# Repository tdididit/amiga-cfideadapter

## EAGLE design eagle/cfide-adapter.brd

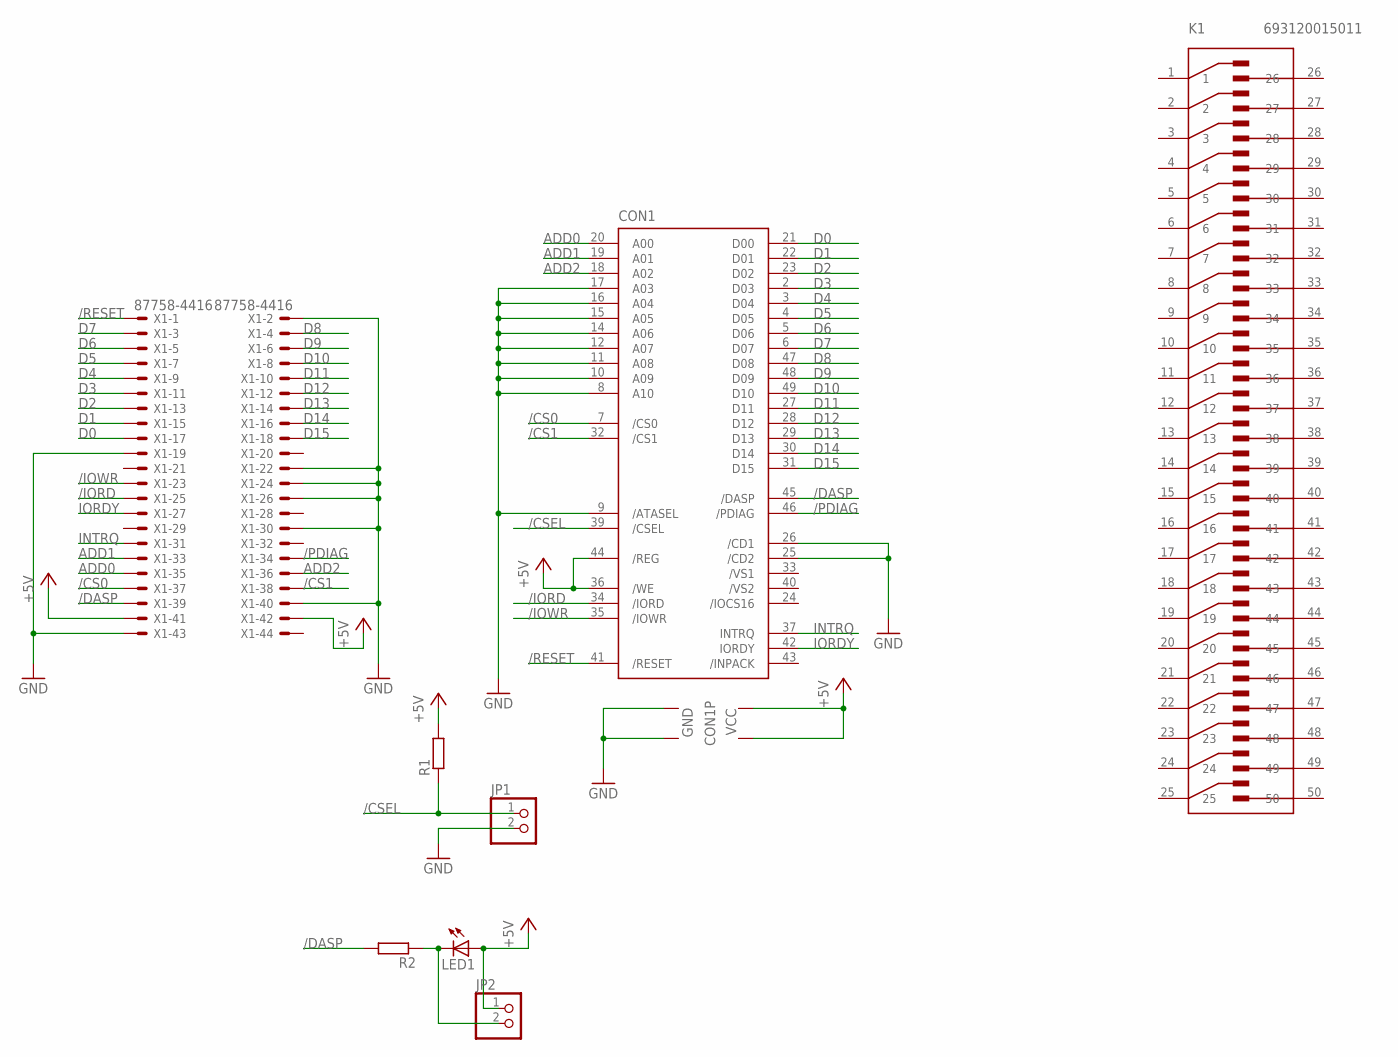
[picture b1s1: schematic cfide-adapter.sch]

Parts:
CON1: CF-CARD-IDE_MODE; MI20-50PD-SF
JP1, JP2: HEADER-1X2ROUND; 1X02_ROUND
K1: 693120015011
LED1: LEDCHIP-LED0603; CHIP-LED0603
R1, R2: R-EU_R0603; R0603
X1: 87758-4416

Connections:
+5V: CON1.13 (VCC2), CON1.36 (/WE), CON1.38 (VCC1), CON1.44 (/REG), JP2.1, LED1.A, R1.2, X1.41, X1.42
/CS0: CON1.7 (/CS0), X1.37
/CS1: CON1.32 (/CS1), X1.38
/CSEL: CON1.39 (/CSEL), JP1.1, R1.1
/DASP: CON1.45 (/DASP), R2.2, X1.39
/IORD: CON1.34 (/IORD), X1.25
/IOWR: CON1.35 (/IOWR), X1.23
/PDIAG: CON1.46 (/PDIAG), X1.34
/RESET: CON1.41 (/RESET), X1.1
ADD0: CON1.20 (A00), X1.35
ADD1: CON1.19 (A01), X1.33
ADD2: CON1.18 (A02), X1.36
D0: CON1.21 (D00), X1.17
D1: CON1.22 (D01), X1.15
D2: CON1.23 (D02), X1.13
D3: CON1.2 (D03), X1.11
D4: CON1.3 (D04), X1.9
D5: CON1.4 (D05), X1.7
D6: CON1.5 (D06), X1.5
D7: CON1.6 (D07), X1.3
D8: CON1.47 (D08), X1.4
D9: CON1.48 (D09), X1.6
D10: CON1.49 (D10), X1.8
D11: CON1.27 (D11), X1.10
D12: CON1.28 (D12), X1.12
D13: CON1.29 (D13), X1.14
D14: CON1.30 (D14), X1.16
D15: CON1.31 (D15), X1.18
GND: CON1.1 (GND1), CON1.8 (A10), CON1.9 (/ATASEL), CON1.10 (A09), CON1.11 (A08), CON1.12 (A07), CON1.14 (A06), CON1.15 (A05), CON1.16 (A04), CON1.17 (A03), CON1.25 (/CD2), CON1.26 (/CD1), CON1.50 (GND2), JP1.2, X1.2, X1.19, X1.22, X1.24, X1.26, X1.30, X1.40, X1.43
INTRQ: CON1.37 (INTRQ), X1.31
IORDY: CON1.42 (IORDY), X1.27
unnamed: JP2.2, LED1.C, R2.1

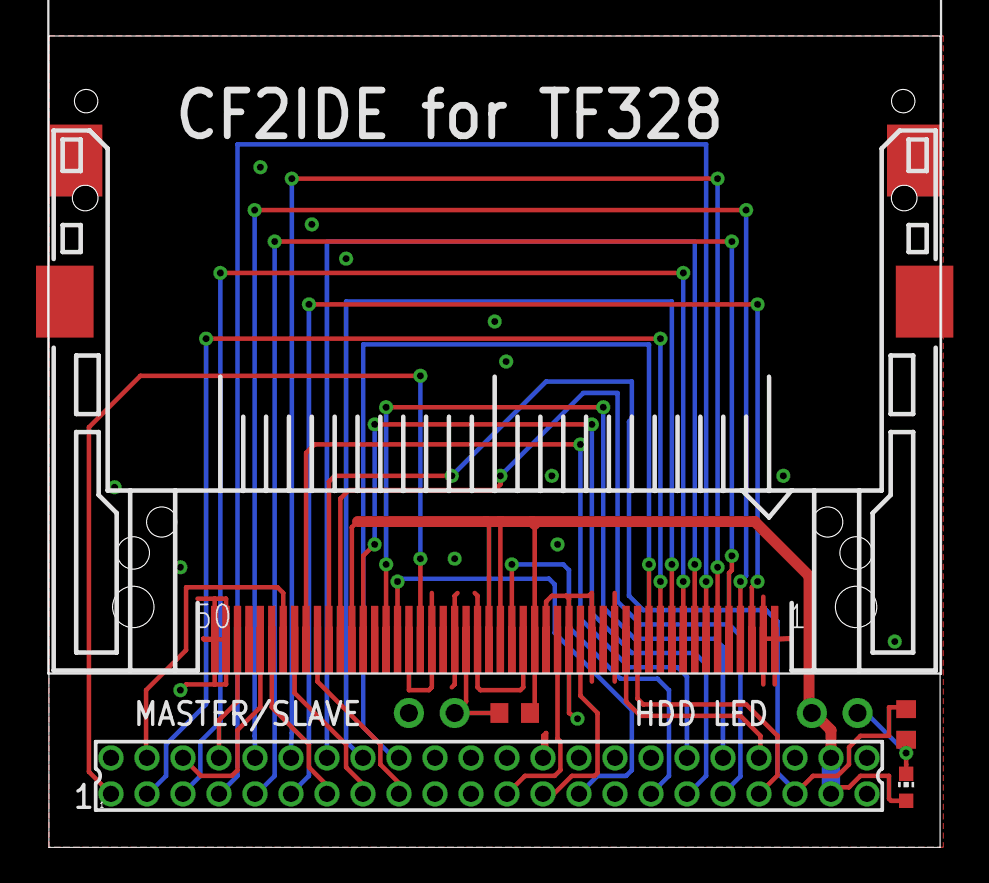
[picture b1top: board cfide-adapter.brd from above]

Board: 2 copper layers, 49.5 x 45.1 mm, 8 parts (0 on the bottom side), 32 nets.

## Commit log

2017-12-22 eagle files

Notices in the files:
parts and their libraries:
microbuilder: This work is placed in the public domain, and may be freely used for commercial and non-commercial work with the following conditions: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
Wuerth_Elektronik_eiCan_Communication_Co: Copyright: Würth Elektronik
